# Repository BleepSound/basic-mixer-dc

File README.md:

[![CC BY-SA 4.0][cc-by-sa-shield]][cc-by-sa]

# basic DC mixer

Latest documentation available at https://bleepsound.github.io/modules/

[![CC BY-SA 4.0][cc-by-sa-image]][cc-by-sa]

[cc-by-sa]: http://creativecommons.org/licenses/by-sa/4.0/
[cc-by-sa-image]: https://licensebuttons.net/l/by-sa/4.0/88x31.png
[cc-by-sa-shield]: https://img.shields.io/badge/License-CC%20BY--SA%204.0-lightgrey.svg

[![CC BY-SA 4.0][cc-by-sa-shield]][cc-by-sa]

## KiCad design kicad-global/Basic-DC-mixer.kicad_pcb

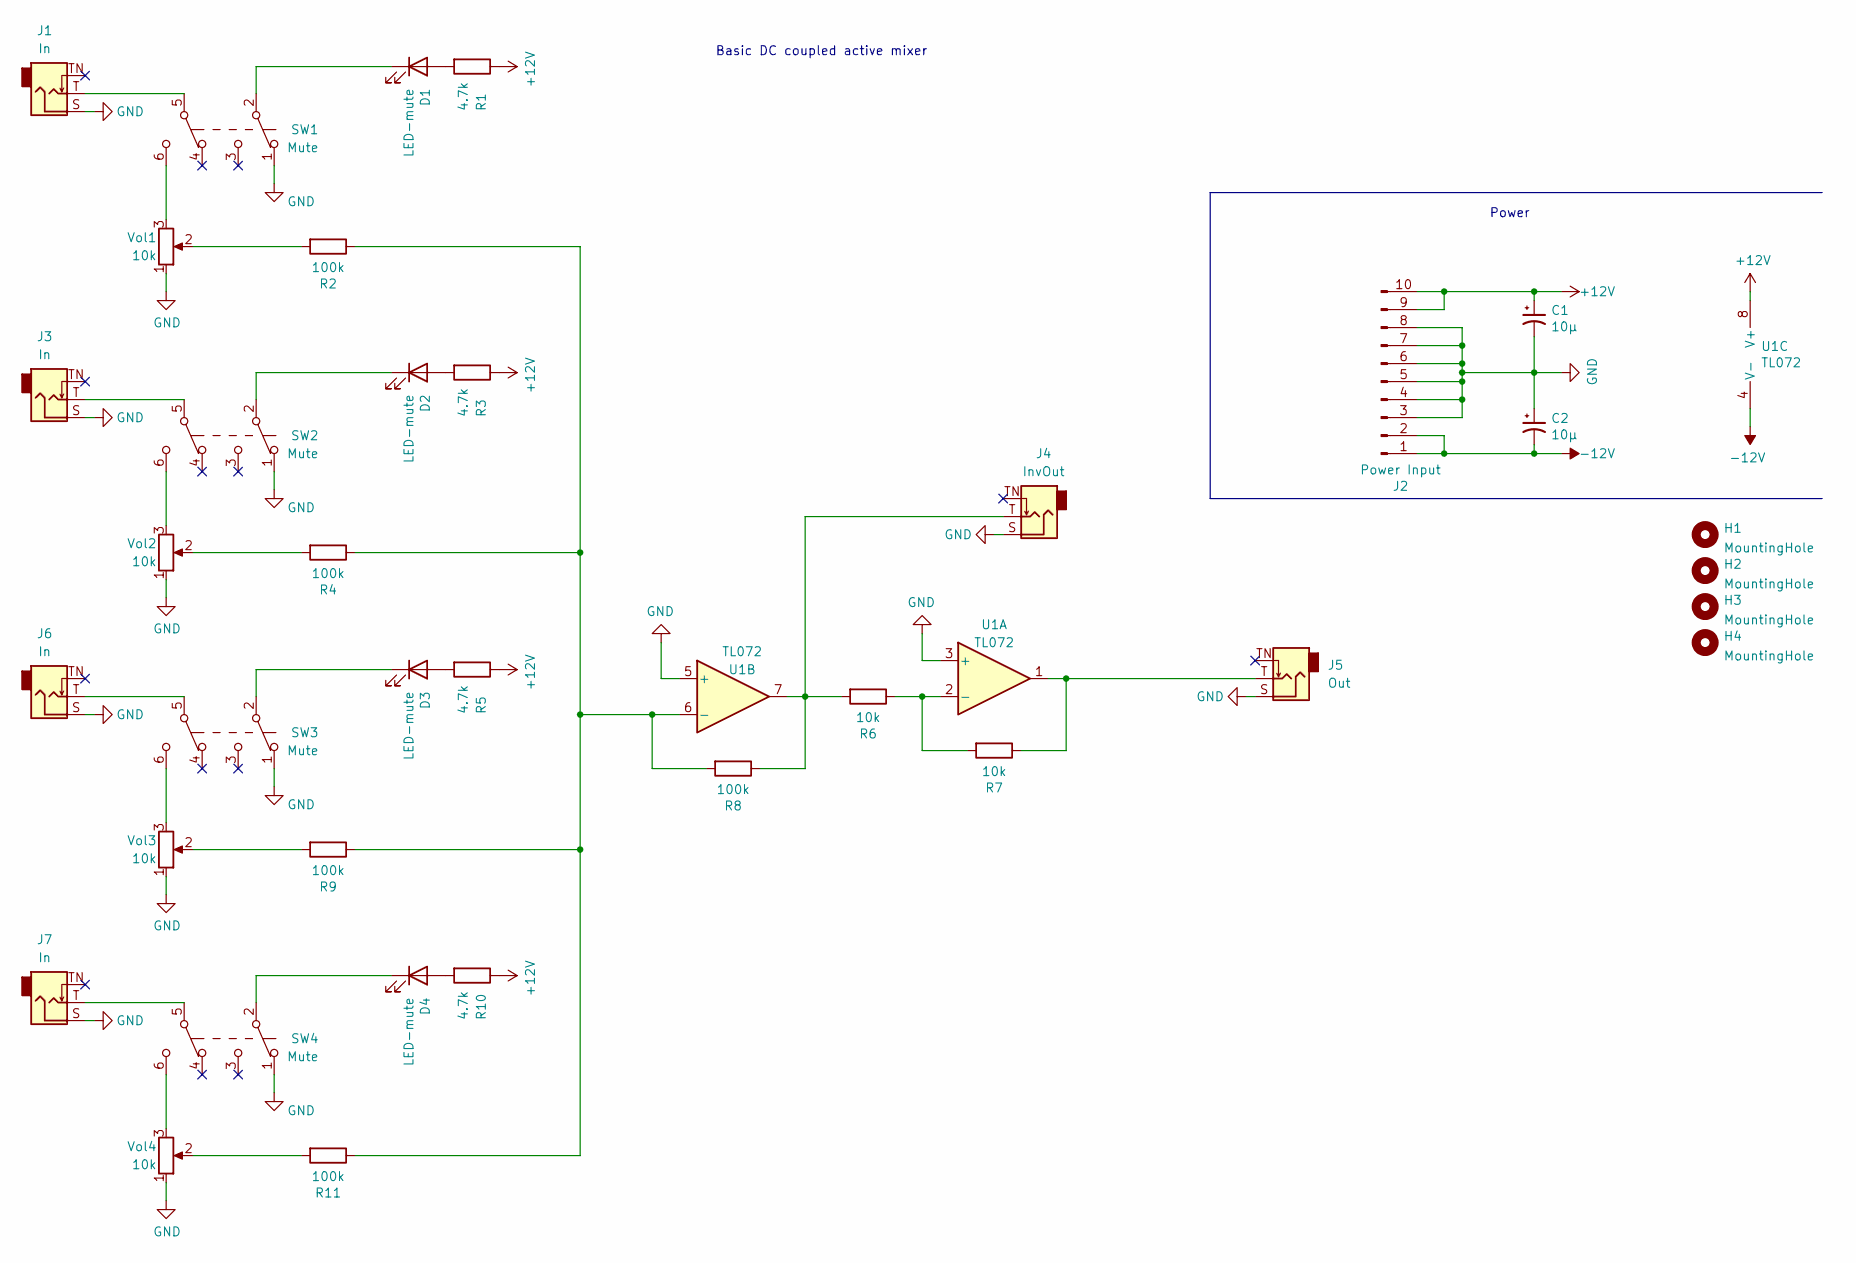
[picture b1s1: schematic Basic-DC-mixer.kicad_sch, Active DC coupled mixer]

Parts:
C1, C2: 10µ; CP_Radial_D5.0mm_P2.00mm
D1, D2, D3, D4: LED-mute; LED_D4.0mm
H1, H2, H3, H4: MountingHole; Doepfer Mounting hole
J1, J3, J6, J7: In; Thonkiconn
J2: Power Input; IDC-Header_2x05_P2.54mm_Vertical
J4: InvOut; Thonkiconn
J5: Out; Thonkiconn
R1, R3, R5, R10: 4.7k; R_Axial_DIN0207_L6.3mm_D2.5mm_P10.16mm_Horizontal
R2, R4, R8, R9, R11: 100k; R_Axial_DIN0207_L6.3mm_D2.5mm_P10.16mm_Horizontal
R6, R7: 10k; R_Axial_DIN0207_L6.3mm_D2.5mm_P10.16mm_Horizontal
SW1, SW2, SW3, SW4: Mute; SW_DPDT_Toggle
U1: TL072; DIP-8_W7.62mm_Socket
Vol1, Vol2, Vol3, Vol4: 10k; Pot-bourns-alpha

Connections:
+12V: C1.1, J2.9, J2.10, R1.1, R3.1, R5.1, R10.1, U1.8 (V+)
-12V: C2.2, J2.1, J2.2, U1.4 (V-)
GND: C1.2, C2.1, J1.S, J2.3, J2.4, J2.5, J2.6, J2.7, J2.8, J3.S, J4.S, J5.S, J6.S, J7.S, SW1.1 (A), SW2.1 (A), SW3.1 (A), SW4.1 (A), U1.3 (+), U1.5 (+), Vol1.1, Vol2.1, Vol3.1, Vol4.1
unnamed: D1.2 (A), R1.2
unnamed: D1.1 (K), SW1.2 (B)
unnamed: D2.2 (A), R3.2
unnamed: D2.1 (K), SW2.2 (B)
unnamed: D3.2 (A), R5.2
unnamed: D3.1 (K), SW3.2 (B)
unnamed: D4.2 (A), R10.2
unnamed: D4.1 (K), SW4.2 (B)
unnamed: J1.T, SW1.5 (B)
unnamed: J3.T, SW2.5 (B)
unnamed: J4.T, R6.2, R8.1, U1.7
unnamed: J5.T, R7.1, U1.1
unnamed: J6.T, SW3.5 (B)
unnamed: J7.T, SW4.5 (B)
unnamed: R2.2, Vol1.2
unnamed: R4.2, Vol2.2
unnamed: R9.2, Vol3.2
unnamed: R11.2, Vol4.2
unnamed: SW1.6 (C), Vol1.3
unnamed: SW2.6 (C), Vol2.3
unnamed: SW3.6 (C), Vol3.3
unnamed: SW4.6 (C), Vol4.3
unnamed: R6.1, R7.2, U1.2 (-)
unnamed: R2.1, R4.1, R8.2, R9.1, R11.1, U1.6 (-)

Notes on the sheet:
Power
Basic DC coupled active mixer

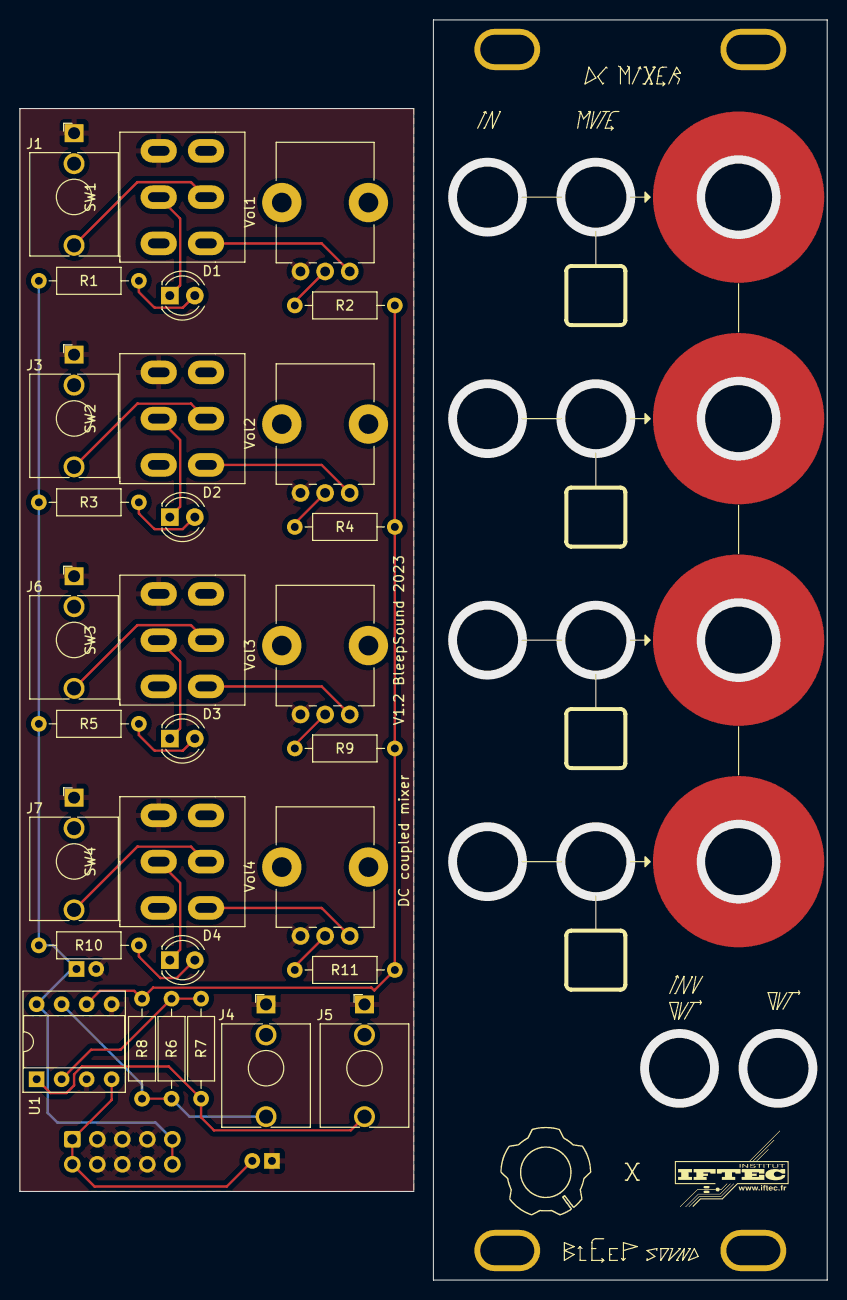
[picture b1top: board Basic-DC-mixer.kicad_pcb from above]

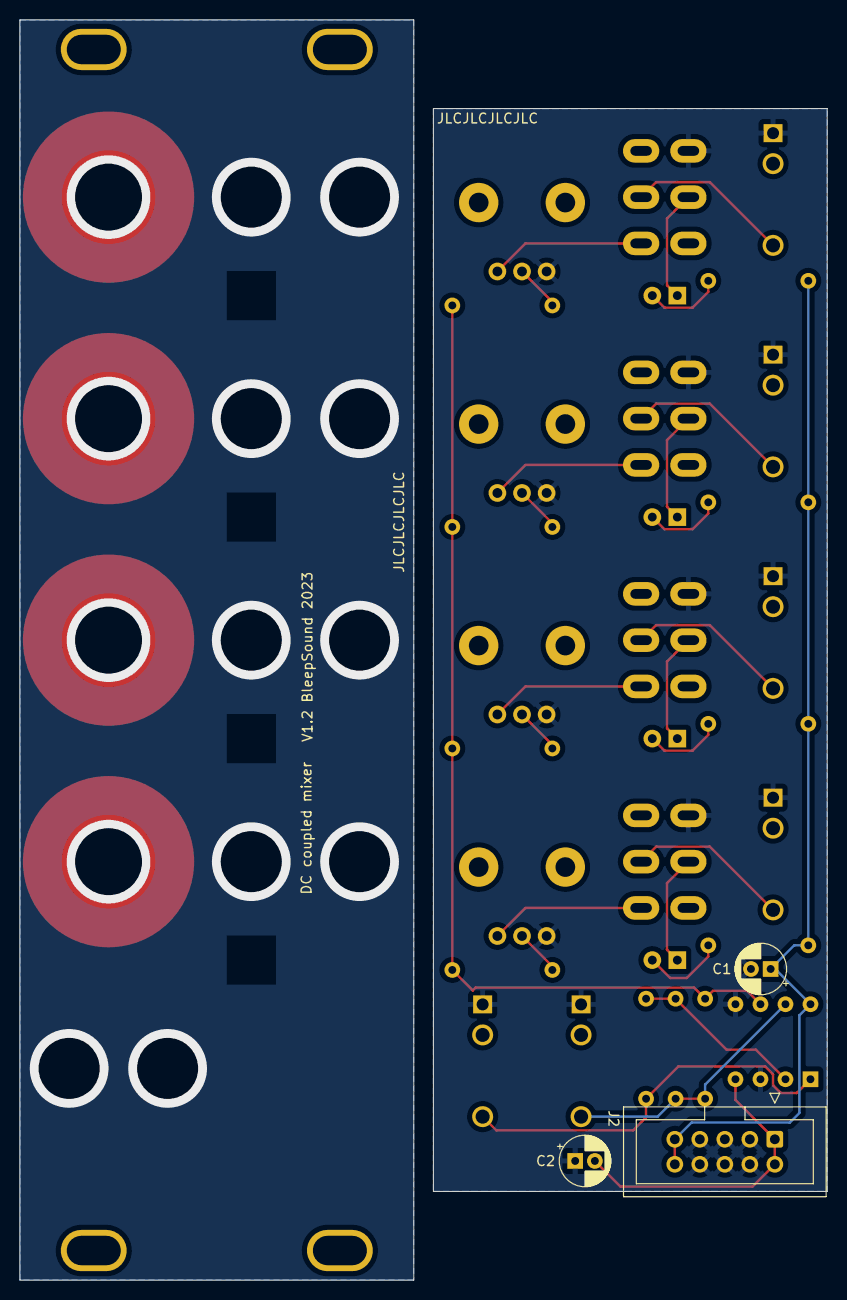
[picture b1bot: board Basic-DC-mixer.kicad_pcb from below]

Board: 2 copper layers, 82.0 x 128.0 mm, 37 parts (3 on the bottom side), 27 nets.

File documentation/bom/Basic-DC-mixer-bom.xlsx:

|  | KiBot Bill of Materials
 |  | Schematic: | Basic-DC-mixer | Component Groups: | 10
 |  | Variant: | default | Component Count: | 33 (0 SMD/ 33 THT)
 |  | Revision: |  | Fitted Components: | 33 (0 SMD/ 33 THT)
 |  | Date: | 2023-06-10_15-38-43 | Number of PCBs: | 1
 |  | KiCad Version: | 7.0.5.1-1-g8f565ef7f0-dirty-deb11 | Total Components: | 33
Row | Description | References | Value | Footprint | Quantity Per PCB | Comment
1 |  | C1 C2 | 10µ | CP_Radial_D5.0mm_P2.00mm | 2
2 | Light emitting diode | D1 D2 D3 D4 | LED-mute | LED_D4.0mm | 4
3 | Audio Jack, 2 Poles (Mono / TS), Switched Pole (Normalling) | J1 J3 J4 J5 J6 J7 | In | Thonkiconn | 6
4 | Generic connector, single row, 01x10, script generated (kicad-library-utils/sch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 | J2 | Power Input | PinHeader_2x05_P2.54mm_Vertical | 1
5 | Resistor | R1 R3 R5 R10 | 4.7k | R_Axial_DIN0207_L6.3mm_D2.5mm_P10.16mm_Horizontal | 4
6 | Resistor | R6 R7 | 10k | R_Axial_DIN0207_L6.3mm_D2.5mm_P10.16mm_Horizontal | 2
7 | Resistor | R2 R4 R8 R9 R11 | 100k | R_Axial_DIN0207_L6.3mm_D2.5mm_P10.16mm_Horizontal | 5
8 | Momentary Switch, dual pole double throw | SW1 SW2 SW3 SW4 | Mute | SW_DPDT_Toggle | 4
9 | Dual Low-Noise JFET-Input Operational Amplifiers, DIP-8/SOIC-8 | U1 | TL072 | DIP-8_W7.62mm_Socket | 1
10 |  | Vol1 Vol2 Vol3 Vol4 | 10k | Pot-bourns-alpha | 4

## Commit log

2023-01-12 add jack gerber
2023-01-12 add main BoM and images
2023-01-12 add front gerber
2023-01-12 add jack BoM
2023-01-13 Remove jekyll workflow
2023-01-13 Add theme
2023-01-13 Try to fix images links
2023-01-14 mise a jour guide montage
2023-06-10 update silkscreen and hole diameter
2023-06-10 update workflow to make it work
2023-10-13 update mixer to v1.2, update repo organization
2024-10-26 Stop github pages hosting
2025-11-27 add licence
